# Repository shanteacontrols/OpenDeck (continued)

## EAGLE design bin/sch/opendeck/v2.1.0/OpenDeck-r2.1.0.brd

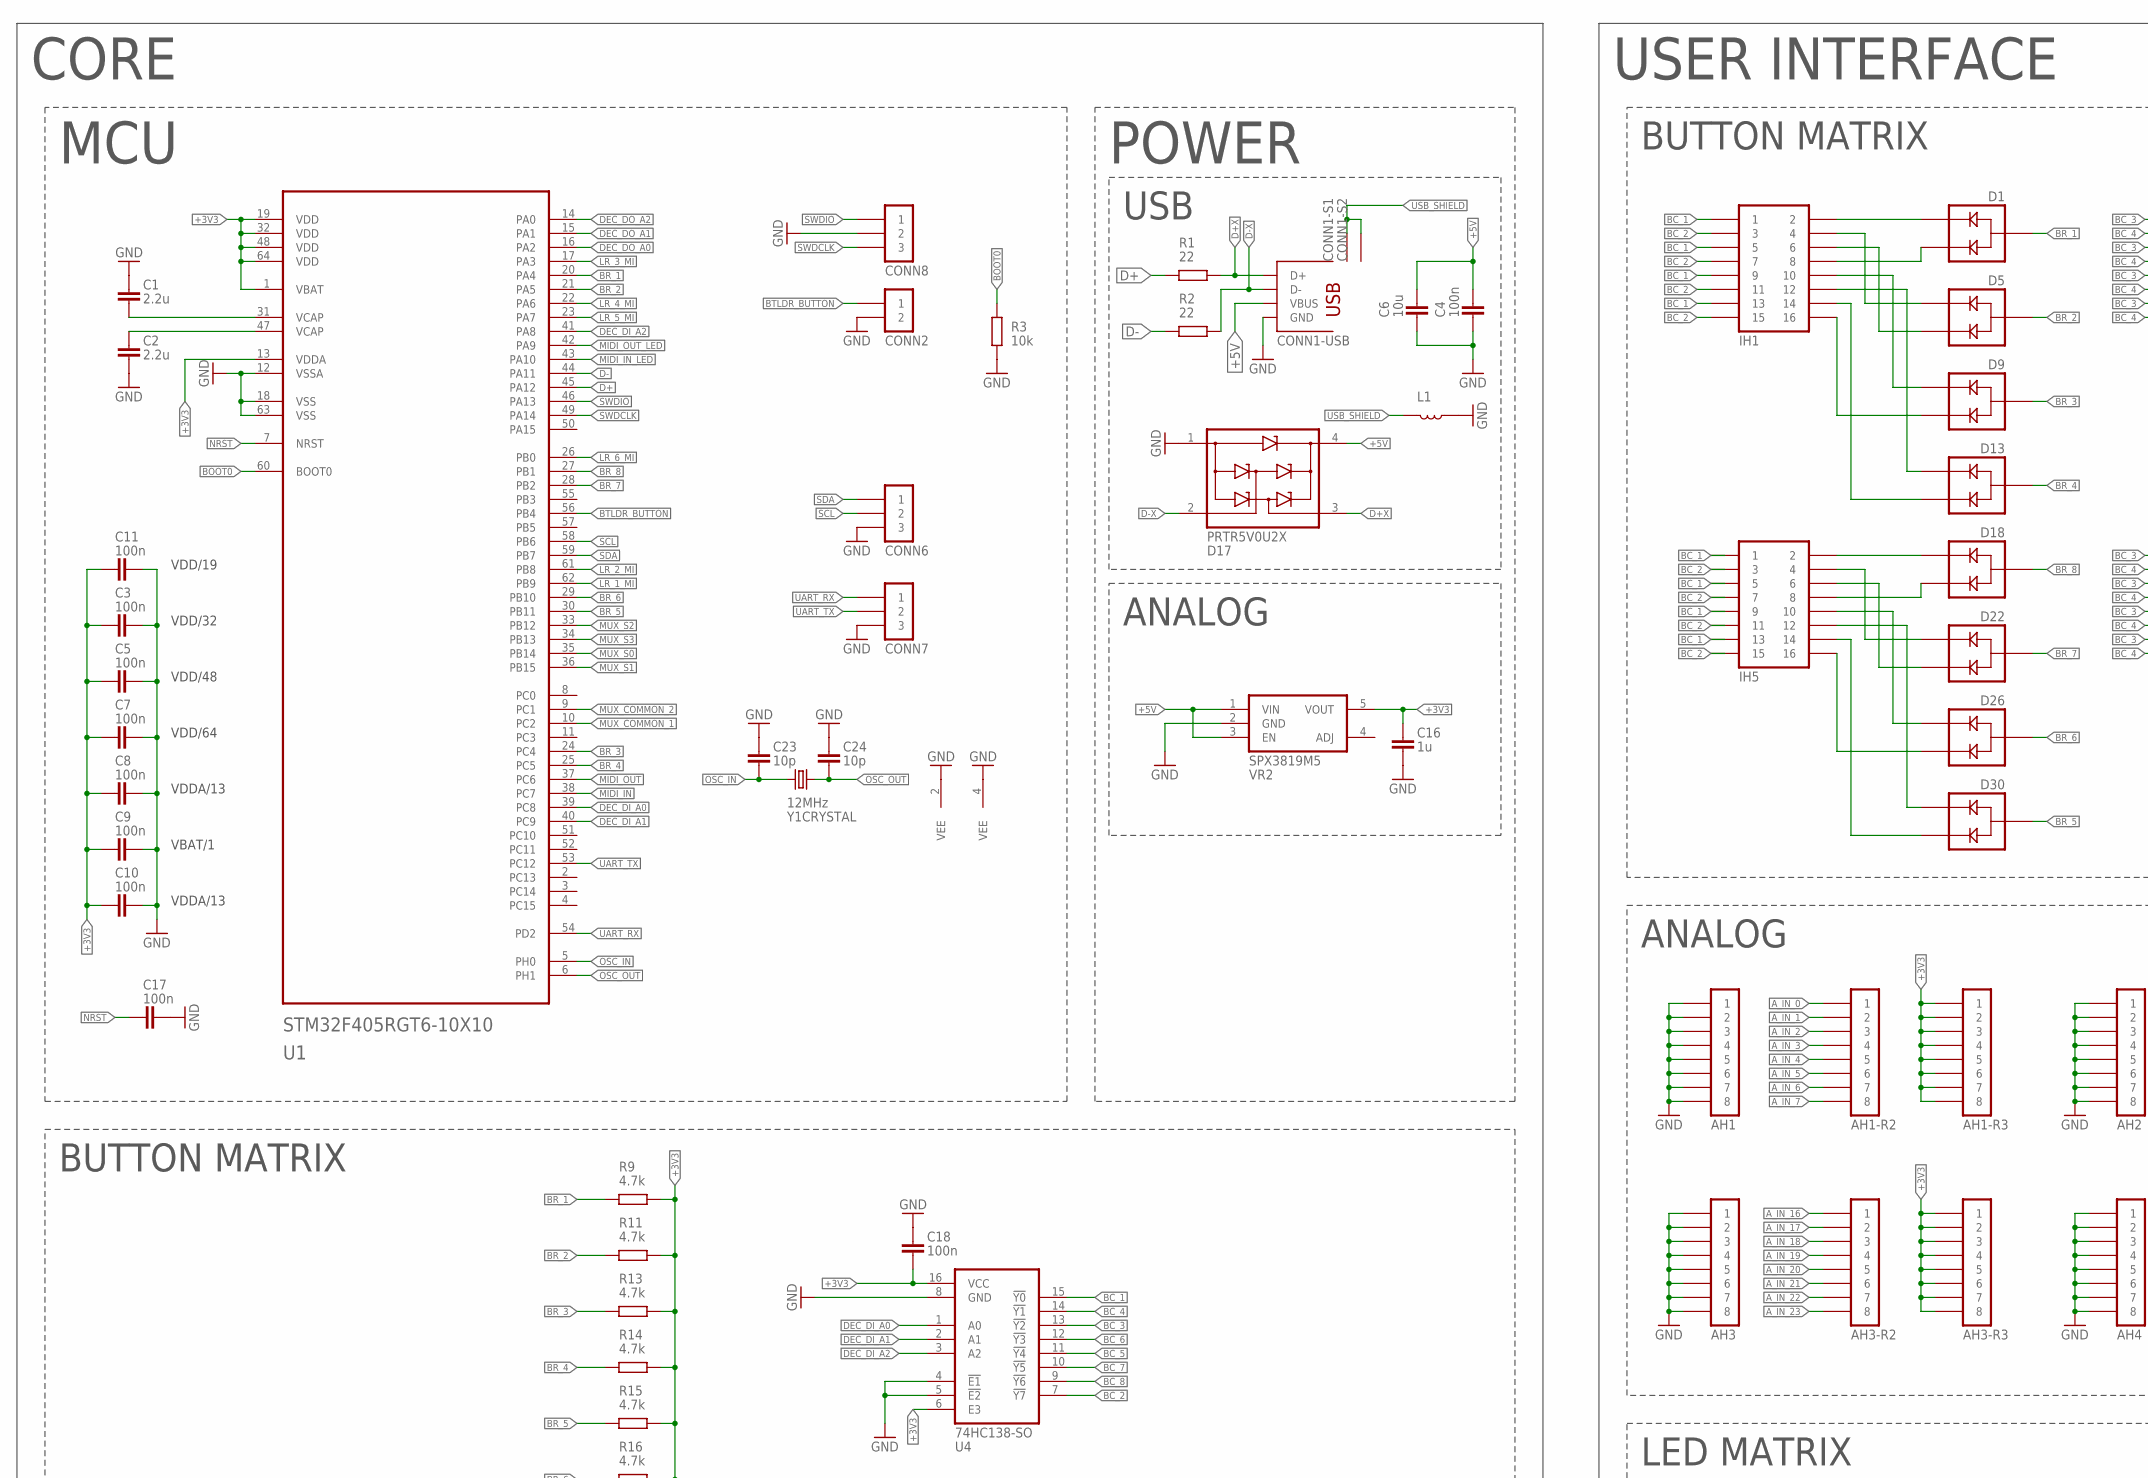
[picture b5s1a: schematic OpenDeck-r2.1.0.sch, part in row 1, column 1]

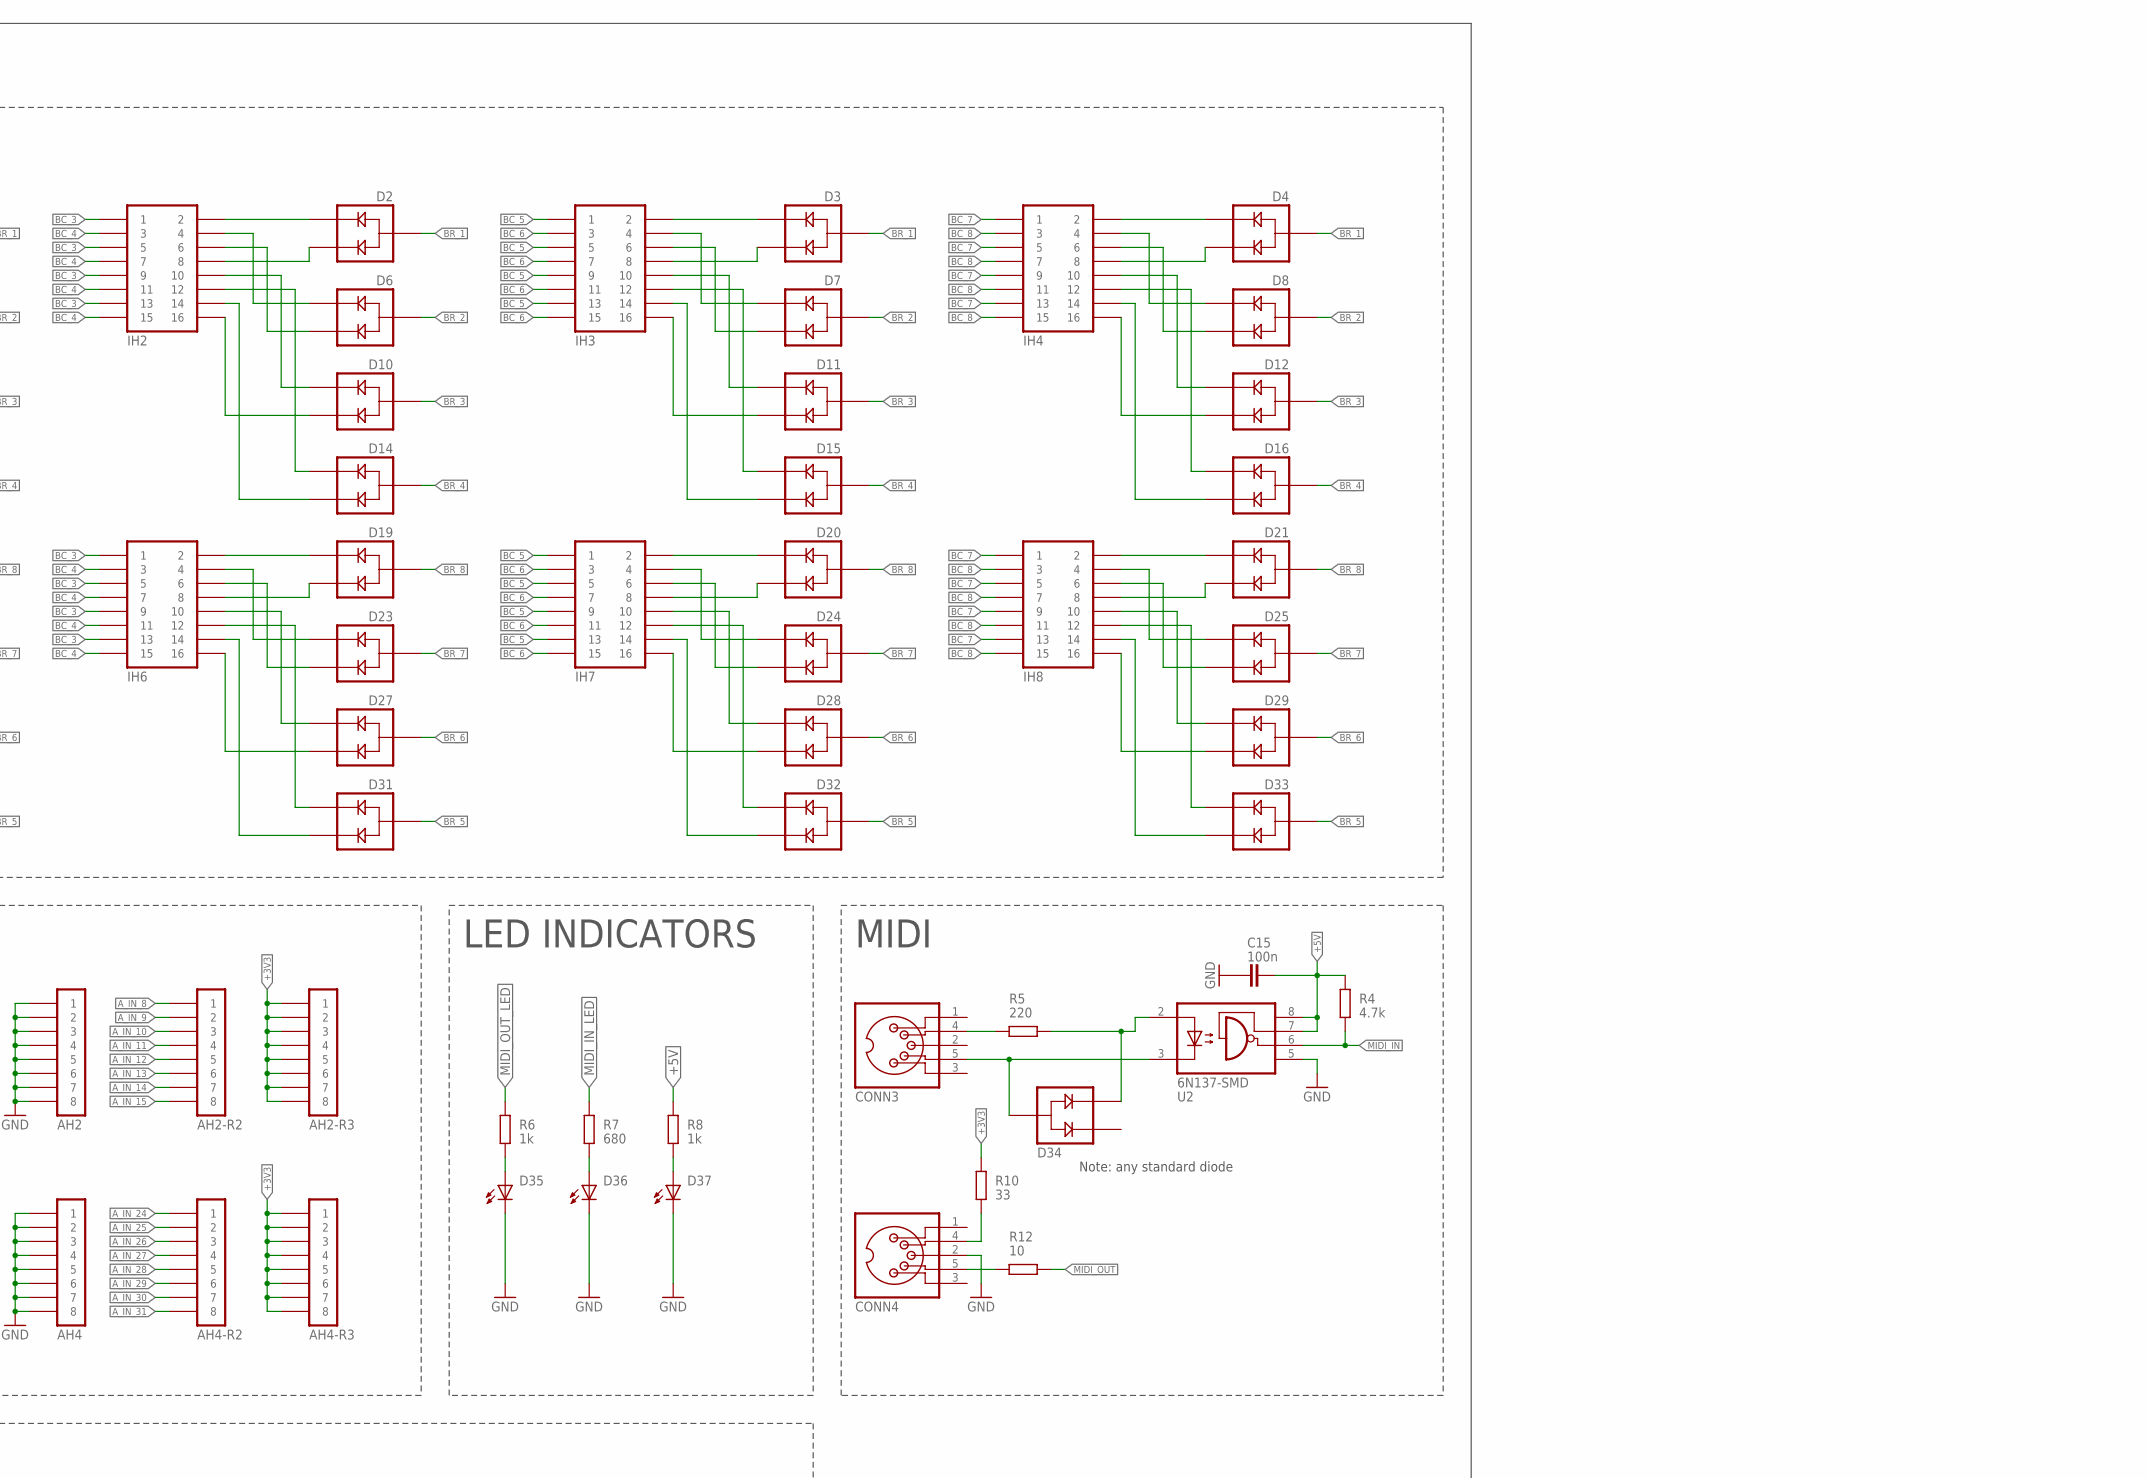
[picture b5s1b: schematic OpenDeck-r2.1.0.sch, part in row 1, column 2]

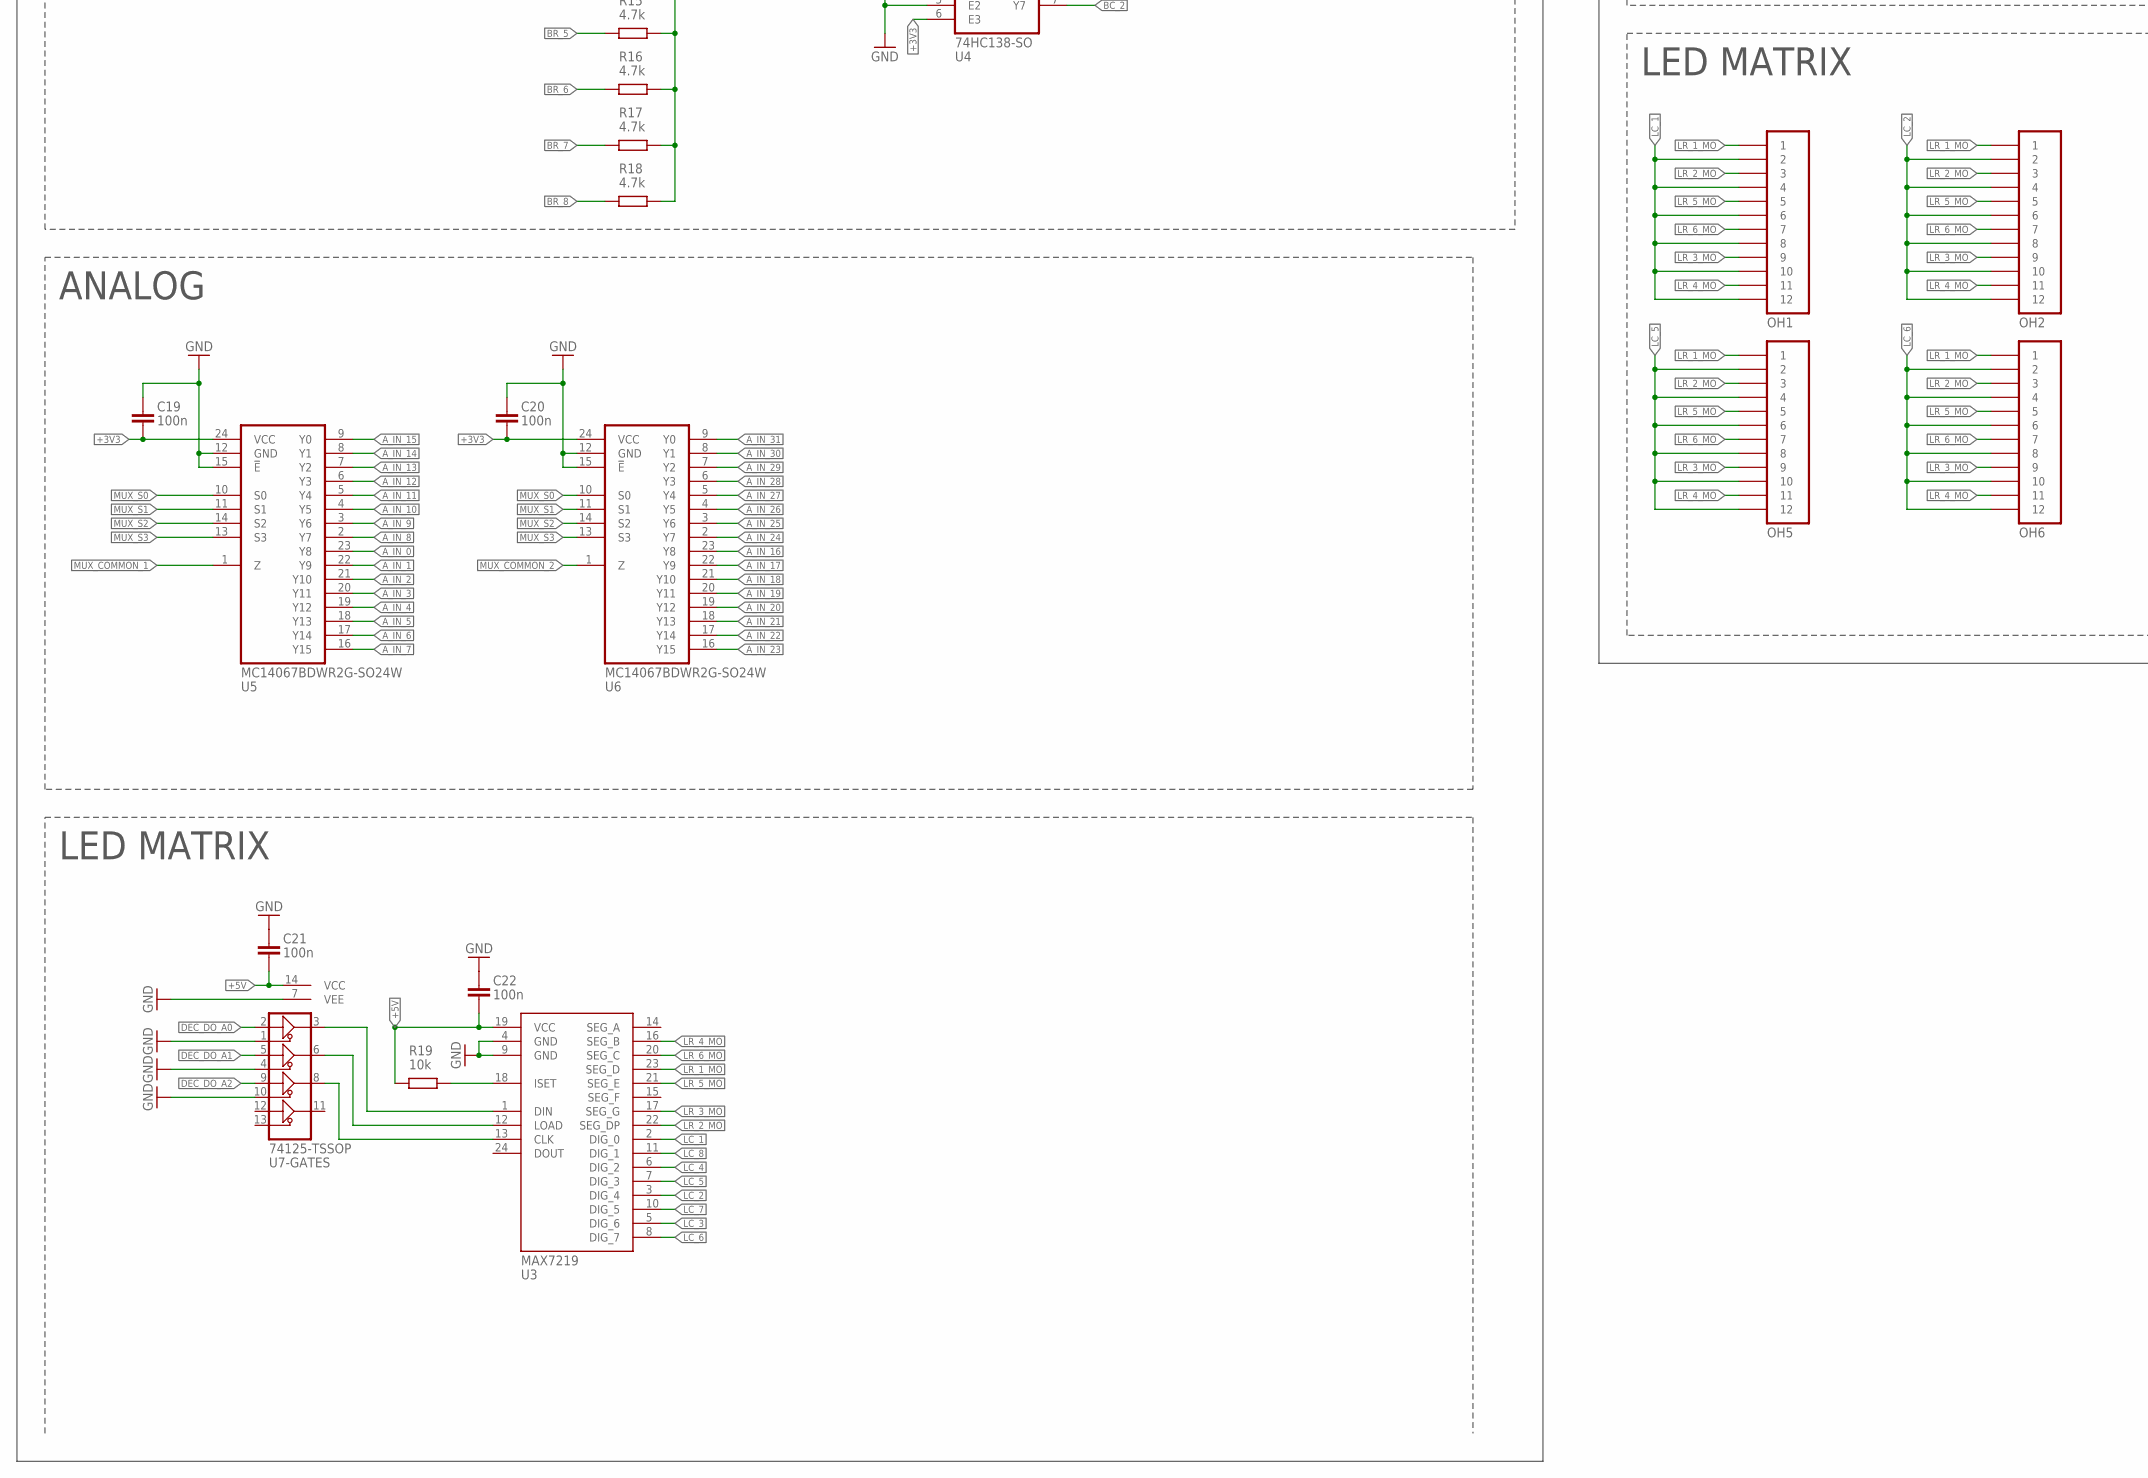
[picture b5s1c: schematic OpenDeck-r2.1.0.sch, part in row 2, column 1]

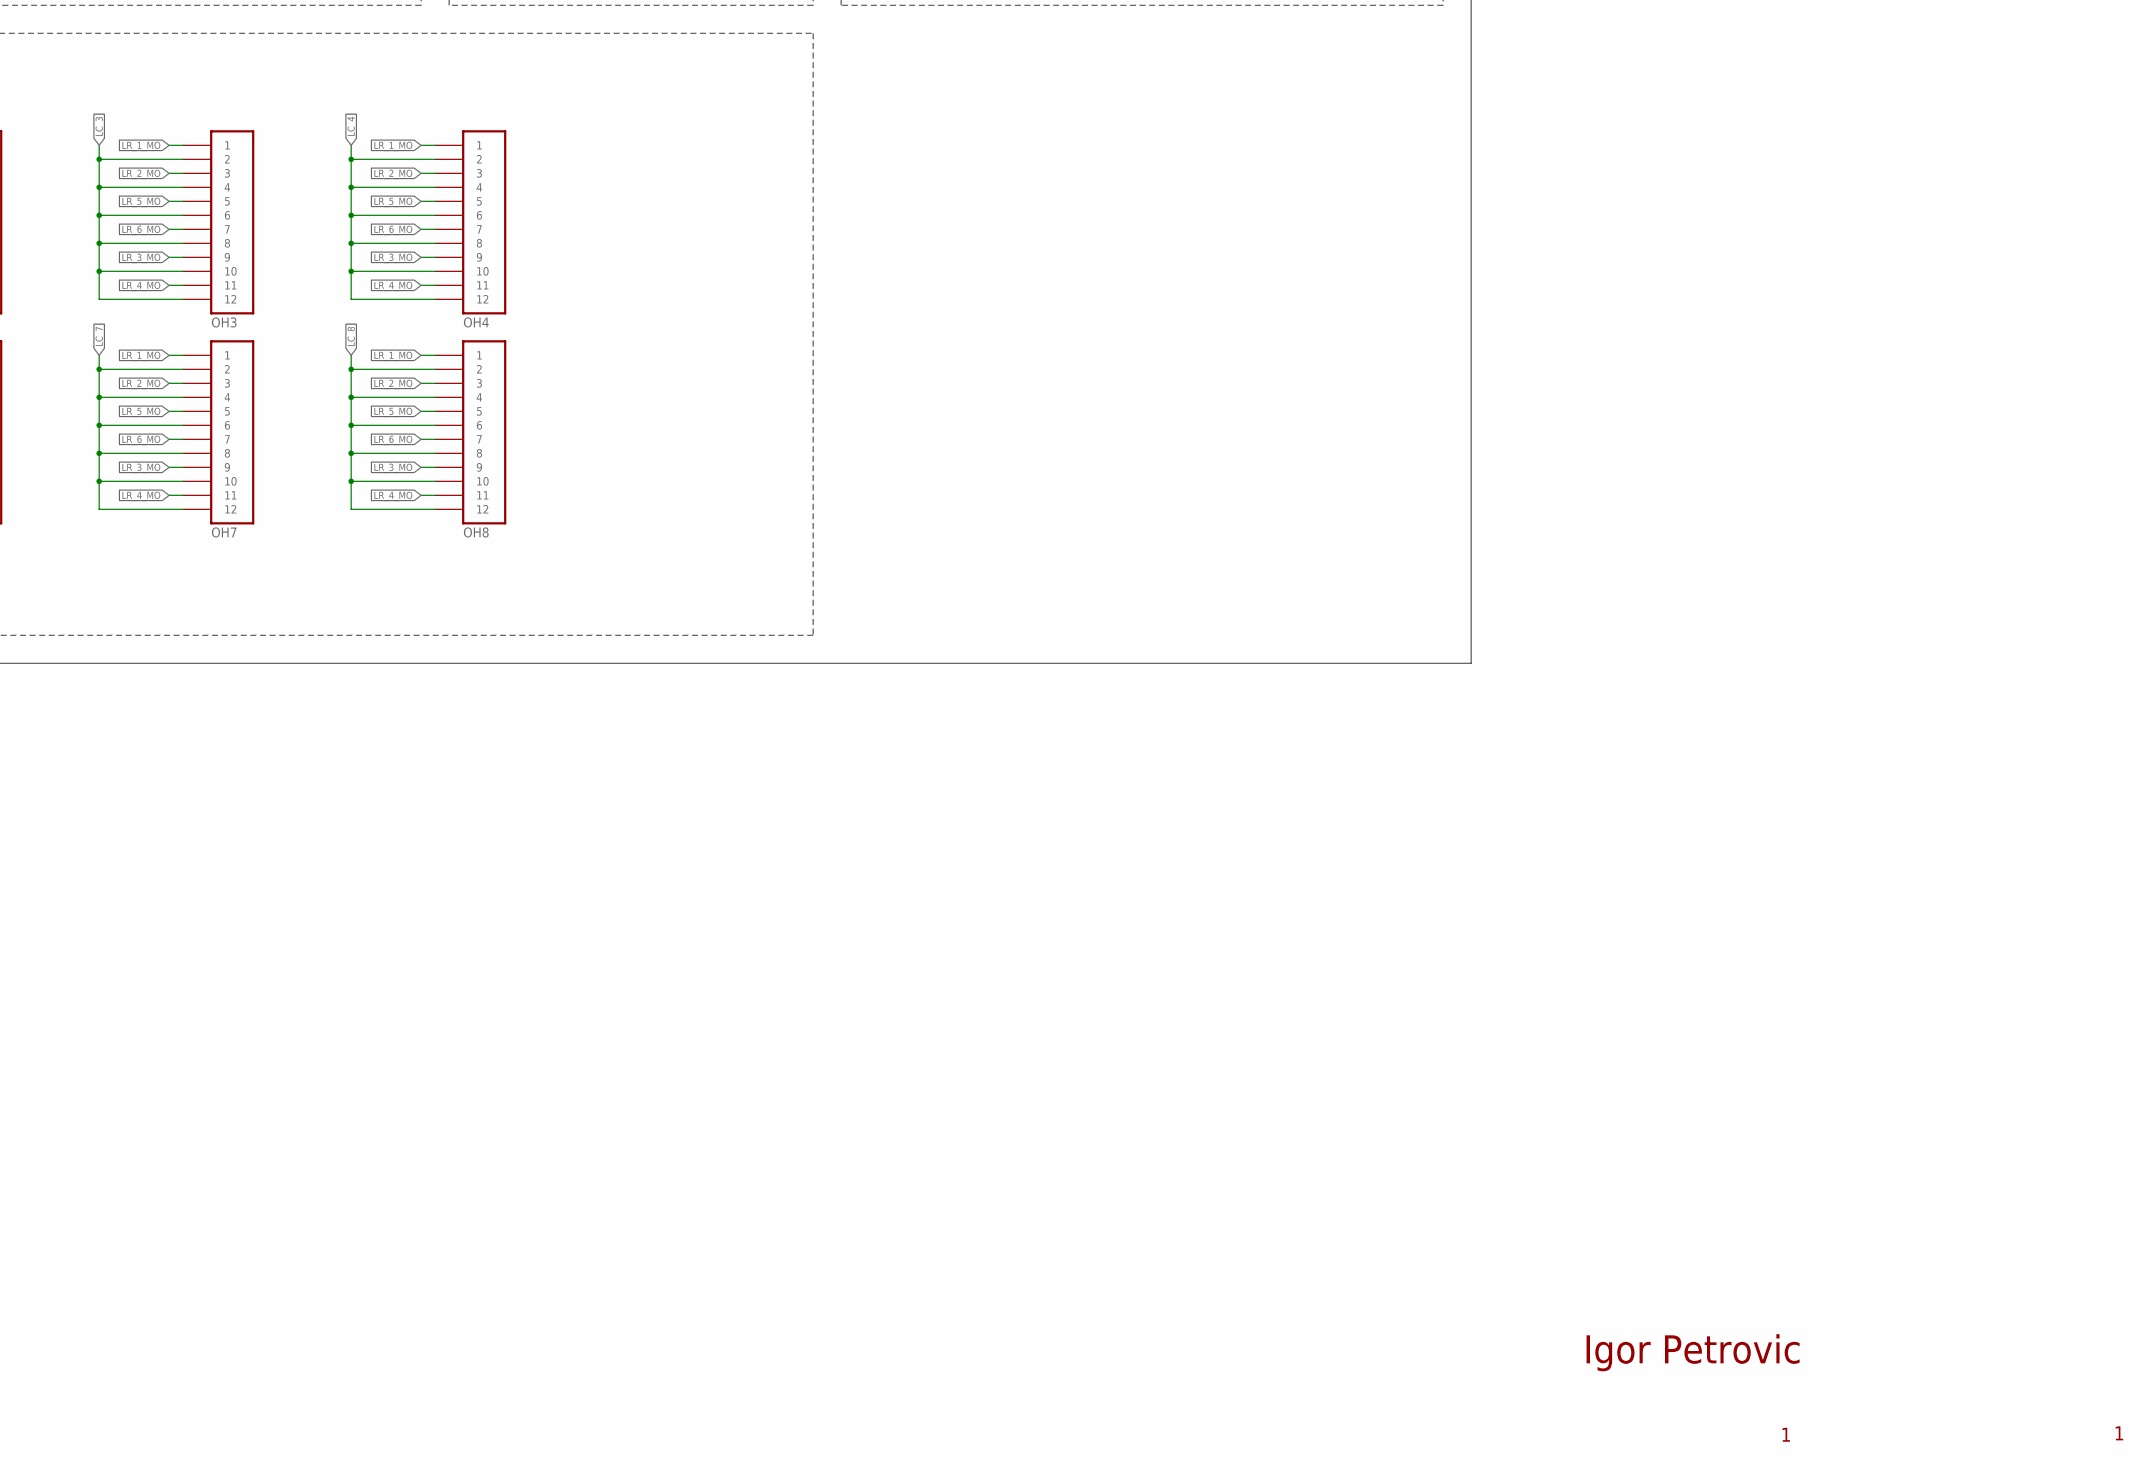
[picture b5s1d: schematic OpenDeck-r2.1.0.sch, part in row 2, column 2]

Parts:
AH1, AH2, AH3, AH4: PINHD-3X08; 3X08-2.54
C1, C2: 2.2u; C0402; LCSC C12530
C3, C4, C5, C7, C8, C9, C10, C11, C15, C17, C18, C19, C20, C21, C22: 100n; C0402; LCSC C1525
C6: 10u; C0402; LCSC C15525
C16: 1u; C0402; LCSC C52923
C23, C24: 10p; C0402; LCSC C32949
CONN1: USB-B-H; USB-B-PTH; LCSC C114097
CONN2: PINHD-1X02-TH-2.54MM; 1X02-2.54-V
CONN3, CONN4: MIDI_CONN-STD; DIN5
CONN6, CONN7, CONN8: PINHD-1X03-TH-2.54MM; 1X03-2.54-V
D1, D2, D3, D4, D5, D6, D7, D8, D9, D10, D11, D12, D13, D14, D15, D16, D18, D19, D20, D21, D22, D23, D24, D25, D26, D27, D28, D29, D30, D31, D32, D33, D34: BAW56; SOT23; LCSC C8663
D17: PRTR5V0U2X; SOT143; LCSC C2827688
D35: Red; 0805_LED; LCSC C84256
D36: Yellow; 0805_LED; LCSC C142303
D37: Green; 0805_LED; LCSC C84256
IH1, IH2, IH3, IH4, IH5, IH6, IH7, IH8: PINHD-2X08-TH-2.54MM; 2X08-2.54
L1: FERRITE_BEAD-BLM21PG221SN1D; L0805; LCSC C85840
OH1, OH2, OH3, OH4, OH5, OH6, OH7, OH8: PINHD-2X06-TH-2.54MM; 2X06-2.54-V
R1, R2: 22; R0402; LCSC C25092
R3, R19: 10k; R0402; LCSC C25744
R4, R9, R11, R13, R14, R15, R16, R17, R18: 4.7k; R0402; LCSC C25900
R5: 220; R0402; LCSC C25091
R6, R8: 1k; R0402; LCSC C11702
R7: 680; R0402; LCSC C25130
R10: 33; R0402; LCSC C25105
R12: 10; R0402; LCSC C25077
U1: STM32F405RGT6-10X10; TQFP-64-10X10; LCSC C15742
U2: 6N137-SMD; SMD-8; LCSC C92651
U3: MAX7219; SO24-W; LCSC C9964
U4: 74HC138-SO; SO16; LCSC C6818
U5, U6: MC14067BDWR2G-SO24W; SO24-W; LCSC C496123
U7: 74125-TSSOP; TSSOP14; LCSC C36365
VR2: SPX3819M5; SOT23-5; LCSC C9055
Y1: 12MHz; CRYSTAL-SMD-2.5X2; LCSC C254284

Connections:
+3V3: AH1.3 (1), AH1.6 (2), AH1.9 (3), AH1.12 (4), AH1.15 (5), AH1.18 (6), AH1.21 (7), AH1.24 (8), AH2.3 (1), AH2.6 (2), AH2.9 (3), AH2.12 (4), AH2.15 (5), AH2.18 (6), AH2.21 (7), AH2.24 (8), AH3.3 (1), AH3.6 (2), AH3.9 (3), AH3.12 (4), AH3.15 (5), AH3.18 (6), AH3.21 (7), AH3.24 (8), AH4.3 (1), AH4.6 (2), AH4.9 (3), AH4.12 (4), AH4.15 (5), AH4.18 (6), AH4.21 (7), AH4.24 (8), C3.1, C5.1, C7.1, C8.1, C9.1, C10.1, C11.1, C16.1, C18.2, C19.2, C20.2, R9.1, R10.2, R11.1, R13.1, R14.1, R15.1, R16.1, R17.1, R18.1, U1.1 (VBAT), U1.13 (VDDA), U1.19 (VDD), U1.32 (VDD), U1.48 (VDD), U1.64 (VDD), U4.6 (E3), U4.16 (VCC), U5.24 (VCC), U6.24 (VCC), VR2.5 (VOUT)
+5V: C4.2, C6.2, C15.2, C21.1, C22.1, CONN1.VBUS, D17.4 (VCC), R4.1, R8.1, R19.2, U2.7 (VE), U2.8 (VCC), U3.19 (VCC), U7.14 (VCC), VR2.1 (VIN), VR2.3 (EN)
A_IN_0: AH1.2 (1), U5.23 (Y8)
A_IN_1: AH1.5 (2), U5.22 (Y9)
A_IN_2: AH1.8 (3), U5.21 (Y10)
A_IN_3: AH1.11 (4), U5.20 (Y11)
A_IN_4: AH1.14 (5), U5.19 (Y12)
A_IN_5: AH1.17 (6), U5.18 (Y13)
A_IN_6: AH1.20 (7), U5.17 (Y14)
A_IN_7: AH1.23 (8), U5.16 (Y15)
A_IN_8: AH2.2 (1), U5.2 (Y7)
A_IN_9: AH2.5 (2), U5.3 (Y6)
A_IN_10: AH2.8 (3), U5.4 (Y5)
A_IN_11: AH2.11 (4), U5.5 (Y4)
A_IN_12: AH2.14 (5), U5.6 (Y3)
A_IN_13: AH2.17 (6), U5.7 (Y2)
A_IN_14: AH2.20 (7), U5.8 (Y1)
A_IN_15: AH2.23 (8), U5.9 (Y0)
A_IN_16: AH3.2 (1), U6.23 (Y8)
A_IN_17: AH3.5 (2), U6.22 (Y9)
A_IN_18: AH3.8 (3), U6.21 (Y10)
A_IN_19: AH3.11 (4), U6.20 (Y11)
A_IN_20: AH3.14 (5), U6.19 (Y12)
A_IN_21: AH3.17 (6), U6.18 (Y13)
A_IN_22: AH3.20 (7), U6.17 (Y14)
A_IN_23: AH3.23 (8), U6.16 (Y15)
A_IN_24: AH4.2 (1), U6.2 (Y7)
A_IN_25: AH4.5 (2), U6.3 (Y6)
A_IN_26: AH4.8 (3), U6.4 (Y5)
A_IN_27: AH4.11 (4), U6.5 (Y4)
A_IN_28: AH4.14 (5), U6.6 (Y3)
A_IN_29: AH4.17 (6), U6.7 (Y2)
A_IN_30: AH4.20 (7), U6.8 (Y1)
A_IN_31: AH4.23 (8), U6.9 (Y0)
BC_1: IH1.1, IH1.5, IH1.9, IH1.13, IH5.1, IH5.5, IH5.9, IH5.13, U4.15 (!Y0)
BC_2: IH1.3, IH1.7, IH1.11, IH1.15, IH5.3, IH5.7, IH5.11, IH5.15, U4.7 (!Y7)
BC_3: IH2.1, IH2.5, IH2.9, IH2.13, IH6.1, IH6.5, IH6.9, IH6.13, U4.13 (!Y2)
BC_4: IH2.3, IH2.7, IH2.11, IH2.15, IH6.3, IH6.7, IH6.11, IH6.15, U4.14 (!Y1)
BC_5: IH3.1, IH3.5, IH3.9, IH3.13, IH7.1, IH7.5, IH7.9, IH7.13, U4.11 (!Y4)
BC_6: IH3.3, IH3.7, IH3.11, IH3.15, IH7.3, IH7.7, IH7.11, IH7.15, U4.12 (!Y3)
BC_7: IH4.1, IH4.5, IH4.9, IH4.13, IH8.1, IH8.5, IH8.9, IH8.13, U4.10 (!Y5)
BC_8: IH4.3, IH4.7, IH4.11, IH4.15, IH8.3, IH8.7, IH8.11, IH8.15, U4.9 (!Y6)
BOOT0: R3.2, U1.60 (BOOT0)
BR_1: D1.3, D2.3, D3.3, D4.3, R9.2, U1.20 (PA4)
BR_2: D5.3, D6.3, D7.3, D8.3, R11.2, U1.21 (PA5)
BR_3: D9.3, D10.3, D11.3, D12.3, R13.2, U1.24 (PC4)
BR_4: D13.3, D14.3, D15.3, D16.3, R14.2, U1.25 (PC5)
BR_5: D30.3, D31.3, D32.3, D33.3, R15.2, U1.30 (PB11)
BR_6: D26.3, D27.3, D28.3, D29.3, R16.2, U1.29 (PB10)
BR_7: D22.3, D23.3, D24.3, D25.3, R17.2, U1.28 (PB2)
BR_8: D18.3, D19.3, D20.3, D21.3, R18.2, U1.27 (PB1)
BTLDR_BUTTON: CONN2.1, U1.56 (PB4)
D+: R1.2, U1.45 (PA12)
D+X: CONN1.D+, D17.3 (I/O2), R1.1
D-: R2.1, U1.44 (PA11)
D-X: CONN1.D-, D17.2 (I/O1), R2.2
DEC_DI_A0: U1.39 (PC8), U4.1 (A0)
DEC_DI_A1: U1.40 (PC9), U4.2 (A1)
DEC_DI_A2: U1.41 (PA8), U4.3 (A2)
GND: AH1.1, AH1.4 (2), AH1.7 (3), AH1.10 (4), AH1.13 (5), AH1.16 (6), AH1.19 (7), AH1.22 (8), AH2.1, AH2.4 (2), AH2.7 (3), AH2.10 (4), AH2.13 (5), AH2.16 (6), AH2.19 (7), AH2.22 (8), AH3.1, AH3.4 (2), AH3.7 (3), AH3.10 (4), AH3.13 (5), AH3.16 (6), AH3.19 (7), AH3.22 (8), AH4.1, AH4.4 (2), AH4.7 (3), AH4.10 (4), AH4.13 (5), AH4.16 (6), AH4.19 (7), AH4.22 (8), C1.1, C2.2, C3.2, C4.1, C5.2, C6.1, C7.2, C8.2, C9.2, C10.2, C11.2, C15.1, C16.2, C17.2, C18.1, C19.1, C20.1, C21.2, C22.2, C23.2, C24.2, CONN1.GND, CONN2.2, CONN4.2, CONN6.3, CONN7.3, CONN8.2, D17.1 (GND), D35.C, D36.C, D37.C, L1.1, R3.1, U1.12 (VSSA), U1.18 (VSS), U1.63 (VSS), U2.5 (GND), U3.4 (GND), U3.9 (GND), U4.4 (!E1), U4.5 (!E2), U4.8 (GND), U5.12 (GND), U5.15 (!E), U6.12 (GND), U6.15 (!E), U7.1 (1!(OE)), U7.4 (2!(OE)), U7.7 (VEE), U7.10 (3!(OE)), VR2.2 (GND), Y1.2 (VEE), Y1.4 (VEE)
IH1_2: D1.1, IH1.2
IH1_4: D5.1, IH1.4
IH1_6: D5.2, IH1.6
IH1_8: D1.2, IH1.8
IH1_10: D9.1, IH1.10
IH1_12: D13.1, IH1.12
IH1_14: D13.2, IH1.14
IH1_16: D9.2, IH1.16
IH2_2: D2.1, IH2.2
IH2_4: D6.1, IH2.4
IH2_6: D6.2, IH2.6
IH2_8: D2.2, IH2.8
IH2_10: D10.1, IH2.10
IH2_12: D14.1, IH2.12
IH2_14: D14.2, IH2.14
IH2_16: D10.2, IH2.16
IH3_2: D3.1, IH3.2
IH3_4: D7.1, IH3.4
IH3_6: D7.2, IH3.6
IH3_8: D3.2, IH3.8
IH3_10: D11.1, IH3.10
IH3_12: D15.1, IH3.12
IH3_14: D15.2, IH3.14
IH3_16: D11.2, IH3.16
IH4_2: D4.1, IH4.2
IH4_4: D8.1, IH4.4
IH4_6: D8.2, IH4.6
IH4_8: D4.2, IH4.8
IH4_10: D12.1, IH4.10
IH4_12: D16.1, IH4.12
IH4_14: D16.2, IH4.14
IH4_16: D12.2, IH4.16
IH5_2: D18.1, IH5.2
IH5_4: D22.1, IH5.4
IH5_6: D22.2, IH5.6
IH5_8: D18.2, IH5.8
IH5_10: D26.1, IH5.10
IH5_12: D30.1, IH5.12
IH5_14: D30.2, IH5.14
IH5_16: D26.2, IH5.16
IH6_2: D19.1, IH6.2
IH6_4: D23.1, IH6.4
IH6_6: D23.2, IH6.6
IH6_8: D19.2, IH6.8
IH6_10: D27.1, IH6.10
IH6_12: D31.1, IH6.12
IH6_14: D31.2, IH6.14
IH6_16: D27.2, IH6.16
IH7_2: D20.1, IH7.2
IH7_4: D24.1, IH7.4
IH7_6: D24.2, IH7.6
IH7_8: D20.2, IH7.8
IH7_10: D28.1, IH7.10
IH7_12: D32.1, IH7.12
IH7_14: D32.2, IH7.14
IH7_16: D28.2, IH7.16
IH8_2: D21.1, IH8.2
IH8_4: D25.1, IH8.4
IH8_6: D25.2, IH8.6
IH8_8: D21.2, IH8.8
IH8_10: D29.1, IH8.10
IH8_12: D33.1, IH8.12
IH8_14: D33.2, IH8.14
IH8_16: D29.2, IH8.16
LC_1: OH1.2, OH1.4, OH1.6, OH1.8, OH1.10, OH1.12, U3.2 (DIG_0)
LC_2: OH2.2, OH2.4, OH2.6, OH2.8, OH2.10, OH2.12, U3.3 (DIG_4)
LC_3: OH3.2, OH3.4, OH3.6, OH3.8, OH3.10, OH3.12, U3.5 (DIG_6)
LC_4: OH4.2, OH4.4, OH4.6, OH4.8, OH4.10, OH4.12, U3.6 (DIG_2)
LC_5: OH5.2, OH5.4, OH5.6, OH5.8, OH5.10, OH5.12, U3.7 (DIG_3)
LC_6: OH6.2, OH6.4, OH6.6, OH6.8, OH6.10, OH6.12, U3.8 (DIG_7)
LC_7: OH7.2, OH7.4, OH7.6, OH7.8, OH7.10, OH7.12, U3.10 (DIG_5)
LC_8: OH8.2, OH8.4, OH8.6, OH8.8, OH8.10, OH8.12, U3.11 (DIG_1)
LR_1_MI: U1.62 (PB9)
LR_1_MO: OH1.1, OH2.1, OH3.1, OH4.1, OH5.1, OH6.1, OH7.1, OH8.1, U3.23 (SEG_D)
LR_2_MI: U1.61 (PB8)
LR_2_MO: OH1.3, OH2.3, OH3.3, OH4.3, OH5.3, OH6.3, OH7.3, OH8.3, U3.22 (SEG_DP)
LR_3_MI: U1.17 (PA3)
LR_3_MO: OH1.9, OH2.9, OH3.9, OH4.9, OH5.9, OH6.9, OH7.9, OH8.9, U3.17 (SEG_G)
LR_4_MI: U1.22 (PA6)
LR_4_MO: OH1.11, OH2.11, OH3.11, OH4.11, OH5.11, OH6.11, OH7.11, OH8.11, U3.16 (SEG_B)
LR_5_MI: U1.23 (PA7)
LR_5_MO: OH1.5, OH2.5, OH3.5, OH4.5, OH5.5, OH6.5, OH7.5, OH8.5, U3.21 (SEG_E)
LR_6_MI: U1.26 (PB0)
LR_6_MO: OH1.7, OH2.7, OH3.7, OH4.7, OH5.7, OH6.7, OH7.7, OH8.7, U3.20 (SEG_C)
MAX7219_CLK: U1.14 (PA0), U7.9 (3A)
MAX7219_DIN: U1.16 (PA2), U7.2 (1A)
MAX7219_LOAD: U1.15 (PA1), U7.5 (2A)
MIDI_IN: R4.2, U1.38 (PC7), U2.6 (VO)
MIDI_IN_4: CONN3.4, R5.1
MIDI_IN_5: CONN3.5, D34.3, U2.3 (C)
MIDI_IN_DIODE_OUT: D34.2, R5.2, U2.2 (A)
MIDI_IN_LED: R7.2, U1.43 (PA10)
MIDI_IN_LED_R: D36.A, R7.1
MIDI_OUT: R12.2, U1.37 (PC6)
MIDI_OUT_4: CONN4.4, R10.1
MIDI_OUT_5: CONN4.5, R12.1
MIDI_OUT_LED: R6.2, U1.42 (PA9)
MIDI_OUT_LED_R: D35.A, R6.1
MUX_COMMON_1: U1.10 (PC2), U5.1 (Z)
MUX_COMMON_2: U1.9 (PC1), U6.1 (Z)
MUX_S0: U1.35 (PB14), U5.10 (S0), U6.10 (S0)
MUX_S1: U1.36 (PB15), U5.11 (S1), U6.11 (S1)
MUX_S2: U1.33 (PB12), U5.14 (S2), U6.14 (S2)
MUX_S3: U1.34 (PB13), U5.13 (S3), U6.13 (S3)
unnamed: C1.2, U1.31 (VCAP)
unnamed: C2.1, U1.47 (VCAP)
unnamed: U3.1 (DIN), U7.3 (1Y)
unnamed: U3.12 (LOAD), U7.6 (2Y)
unnamed: U3.13 (CLK), U7.8 (3Y)
unnamed: R19.1, U3.18 (ISET)
NRST: C17.1, U1.7 (NRST)
OSC_IN: C23.1, U1.5 (PH0), Y1.1
OSC_OUT: C24.1, U1.6 (PH1), Y1.3 (2)
PWR_LED_R: D37.A, R8.2
SCL: CONN6.2, U1.58 (PB6)
SDA: CONN6.1, U1.59 (PB7)
SWDCLK: CONN8.3, U1.49 (PA14)
SWDIO: CONN8.1, U1.46 (PA13)
UART_RX: CONN7.1, U1.54 (PD2)
UART_TX: CONN7.2, U1.53 (PC12)
USB_SHIELD: CONN1.S1 (S), CONN1.S2 (S), L1.2

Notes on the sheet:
USB
MCU
POWER
LED MATRIX
BUTTON MATRIX
ANALOG
CORE
USER INTERFACE
LED INDICATORS
MIDI
Igor Petrovic
VDD/19
VDD/32
VDD/48
VDD/64
VBAT/1
VDDA/13
Note: any standard diode

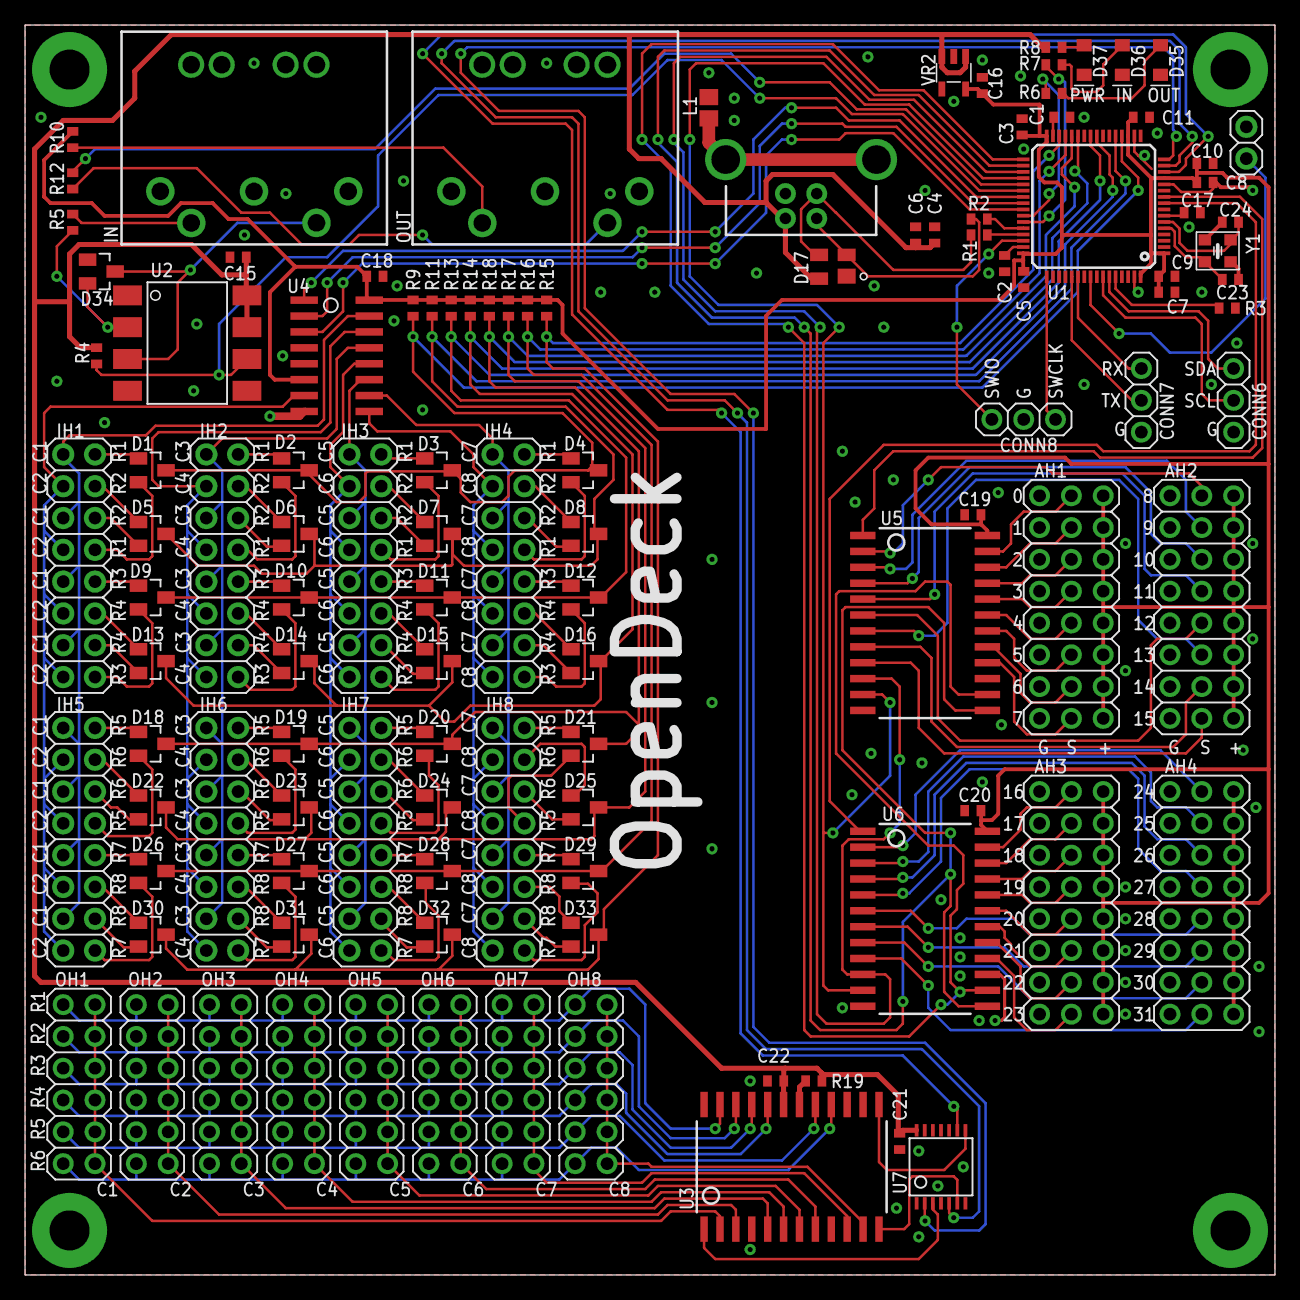
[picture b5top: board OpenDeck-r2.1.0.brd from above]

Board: 2 copper layers, 99.8 x 99.8 mm, 114 parts (0 on the bottom side), 175 nets.

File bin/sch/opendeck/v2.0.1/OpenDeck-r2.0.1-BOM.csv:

Qty,Value,Device,Package,Parts,Description,MANUFACTURER,MPN
1,10,RESISTOR-0402,R0402,R12,Resistor,,
15,100n,CAPACITOR-0402,C0402,"C3, C4, C5, C7, C8, C9, C10, C11, C15, C17, C18, C19, C20, C21, C22",Capacitor,,
1,10k,RESISTOR-0402,R0402,R4,Resistor,,
1,10u,ELECTROLYTIC_CAPACITOR16V-CLV-0405,153CLV-0405,C6,Electrolytic capacitor,Multicomp,MCVVT016M100CA1L
1,16MHz,CRYSTAL-4P-SMD-2.5X2,CRYSTAL-SMD-2.5X2,Y1,Crystal,TXC,8Z-16.000MEEQ-T
2,18p,CAPACITOR-0402,C0402,"C23, C24",Capacitor,,
3,1k,RESISTOR-0402,R0402,"R6, R7, R8",Resistor,,
2,2.2u,CAPACITOR-0402,C0402,"C1, C2",Capacitor,,
2,22,RESISTOR-0402,R0402,"R1, R2",Resistor,,
1,220,RESISTOR-0402,R0402,R5,Resistor,,
1,33,RESISTOR-0402,R0402,R10,Resistor,,
6,36,RESISTOR-0402,R0402,"R20, R22, R24, R26, R28, R30",Resistor,,
14,4.7k,RESISTOR-0402,R0402,"R9, R11, R13, R14, R15, R16, R17, R18, R19, R21, R23, R25, R27, R29",Resistor,,
4,4.7u,CAPACITOR-0402,C0402,"C12, C13, C14, C16",Capacitor,,
1,510,RESISTOR-0402,R0402,R3,Resistor,,
1,6N137,6N137,DIL08,U2,High Speed Optocoupler,Vishay,6N137
1,74HC138-SO,74HC138-SO,SO16,U4,3-to-8 line decoder/demultiplexer; inverting,Nexperia,74HC138D
1,74HC238-SO,74HC238-SO,SO16,U7,74HC238/74HCT238,Nexperia,74HC238D
33,BAW56,BAW56,SOT23,"D1, D2, D3, D4, D5, D6, D7, D8, D9, D10, D11, D12, D13, D14, D15, D16, D18, D19, D20, D21, D22, D23, D24, D25, D26, D27, D28, D29, D30, D31, D32, D33, D34",Small Signal Diode,Multicomp,BAW56-7-F
3,FDC6312P,FDC6312P,SSOT6,"Q1, Q2, Q3",Dual P-channel 1.8V PowerTrench Specified MOSFET,ON Semiconductor,FDC6312P
1,FERRITE_BEAD-BLM21PG221SN1D,FERRITE_BEAD-BLM21PG221SN1D,L0805,L1,Ferrite Bead,Murata,BLM21PG221SN1D
1,Green,LED-0805,0805_LED,D37,LED,,
1,LP5907-4.5V,LP5907-4.5V,SOT23-5,VR1,"Ultra Low-Noise, 250-mA Linear LDO Regulator",Texas Instruments,LP5907MFX-4.5/NOPB
2,MC14067BDWR2G-SO24W,MC14067BDWR2G-SO24W,SO24-W,"U5, U6",16-Channel Analog Multiplexer/Demultiplexer,ON Semiconductor,MC14067BDWR2G
1,MCP1825,MCP1825,SOT223,VR2,"500 mA, Low Voltage, Low Quiescent Current LDO Regulator",Microchip,MCP1825S-3302E/DB
2,MIDI_CONN-STD,MIDI_CONN-STD,DIN5_SUPPORT,"CONN3, CONN4",DIN MIDI connector,,
2,PINHD-1X02-TH-2.54MM,PINHD-1X02-TH-2.54MM,1X02-2.54-V,"CONN2, CONN8",Pin Header,,
2,PINHD-1X03-TH-2.54MM,PINHD-1X03-TH-2.54MM,1X03-2.54-V,"CONN6, CONN7",Pin Header,,
1,PINHD-1X04-TH-2.54MM,PINHD-1X04-TH-2.54MM,1X04-2.54,CONN5,Pin Header,,
8,PINHD-2X06-TH-2.54MM,PINHD-2X06-TH-2.54MM,2X06-2.54-V,"OH1, OH2, OH3, OH4, OH5, OH6, OH7, OH8",Pin Header,,
8,PINHD-2X08-TH-2.54MM,PINHD-2X08-TH-2.54MM,2X08-2.54,"IH1, IH2, IH3, IH4, IH5, IH6, IH7, IH8",Pin Header,,
4,PINHD-3X08,PINHD-3X08,3X08-2.54,"AH1, AH2, AH3, AH4",Pin header,,
1,PRTR5V0U2X,PRTR5V0U2X,SOT143,D17,Ultra low capacitance double rail-to-rail ESD protection diode,Nexperia,PRTR5V0U2X
1,Red,LED-0805,0805_LED,D35,LED,,
1,STM32F405RGT6,STM32F405RGT6,TQFP-64-10X10,U1,ARM Cortex-M4 32b MCU+FPU,ST Microelectronics,STM32F405RGT6
1,ULN2803A-SO,ULN2803A-SO,SO18,U8,ULN2803A Darlington Transistor Arrays,Texas Instruments,ULN2803ADWR
1,USB-H,USB-H,USB-B-PTH,CONN1,"USB B connector, horizontal",,
1,Yellow,LED-0805,0805_LED,D36,LED,,

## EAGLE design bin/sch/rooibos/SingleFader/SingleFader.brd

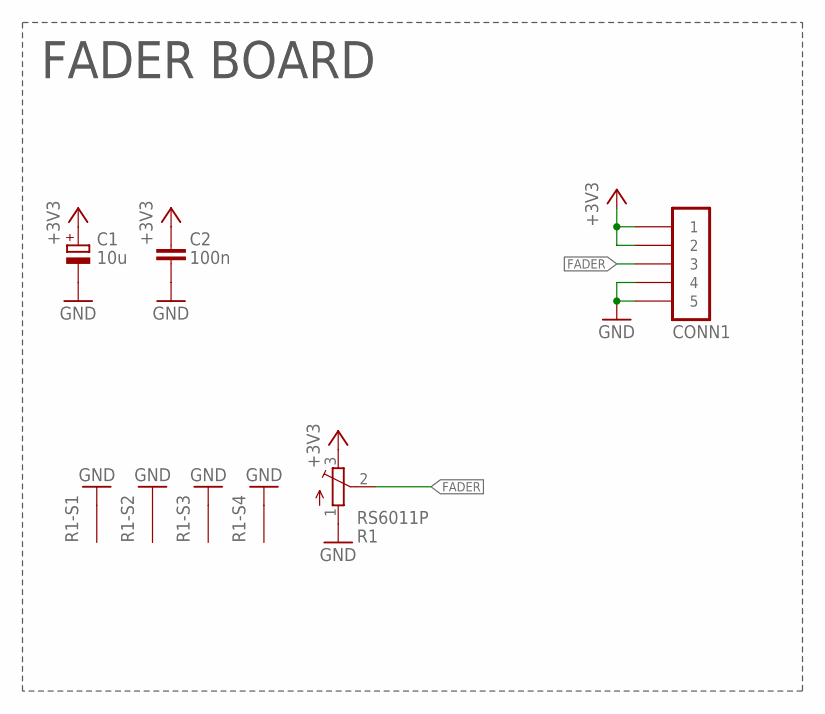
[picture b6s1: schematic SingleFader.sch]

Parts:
C1: 10u; 153CLV-0405
C2: 100n; C0805
CONN1: PINHD-1X05-FFC-1MM-Z; MOLEX-52271-0579
R1: RS6011P; RS6011*P

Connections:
+3V3: C1.+, C2.1, CONN1.1, CONN1.2, R1.3
FADER: CONN1.3, R1.2
GND: C1.-, C2.2, CONN1.4, CONN1.5, R1.1, R1.S1 (S), R1.S2 (S), R1.S3 (S), R1.S4 (S)

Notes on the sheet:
FADER BOARD
